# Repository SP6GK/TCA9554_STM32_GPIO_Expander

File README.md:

# TCA9554 STM32 GPIO Expander

## Software
STM32 HAL driver for the **TCA9554 8-bit I/O expander**. This is a useful IC that I find more capable and easier to use than the common PCF8574.

The project includes:
- HAL based driver
- Demo project in CubeIDE targeting the STM32F411
- KiCad project with eval PCB

### Usage
Copy the .c and .h from demo project to your project:
- TCA9554.c is in /Software/MCU/Src
- TCA9554.h is in /Software/MCU/Inc

Configure the I2C peripheral in STM32CubeMX and initialize the driver:

```c
#include "TCA9554.h"

TCA9554_HandleTypeDef GPIO_expander1 =
{
    .hi2c = &hi2c1,              // CubeMX I2C configuration
    .address = TCA9554_ADDRESS,  // Defined in header file
    .io_configuration = 0x00,    // 0 = Output, 1 = Input
    .io_states = 0x00,           // 0 = Low, 1 = High
    .pol_inversion = 0x00        // No polarity inversion
};

TCA9554_init(&GPIO_expander1);

```

By default, all pins are configured as inputs. Set `io_configuration` to configure individual pins: for example, `0b01010101` configures P0, P2, P4, and P6 as outputs, and P1, P3, P5, and P7 as inputs.

```c
uint8_t read_status = 0;
bool pin_status[8] = {0};

//Write to specific pin
for(int i = 0; i < 8; i++){
		  TCA9554_set_pin(&GPIO_expander1, i, true);
		  HAL_Delay(100);
	  }

//Write state of all pins at once
for(uint8_t counter = 0; counter < UINT8_MAX; counter++){
  TCA9554_write(&GPIO_expander1, TCA9554_OUT_REG, counter);

  read_status = TCA9554_read(&GPIO_expander1, TCA9554_IN_REG);	//Read status of every pin
  for(uint8_t i = 0; i < 8; i++){
  pin_status[i] = TCA9554_read_pin(&GPIO_expander1, i); //Read status of single pin
}

```

## Hardware

KiCad evaluation board design for the **TCA9554 I/O expander**.

The hardware project includes the schematic and PCB design files, organized under the `ECAD/` directory.
`Documents/` includes interactive BOM and .pdf schematic.

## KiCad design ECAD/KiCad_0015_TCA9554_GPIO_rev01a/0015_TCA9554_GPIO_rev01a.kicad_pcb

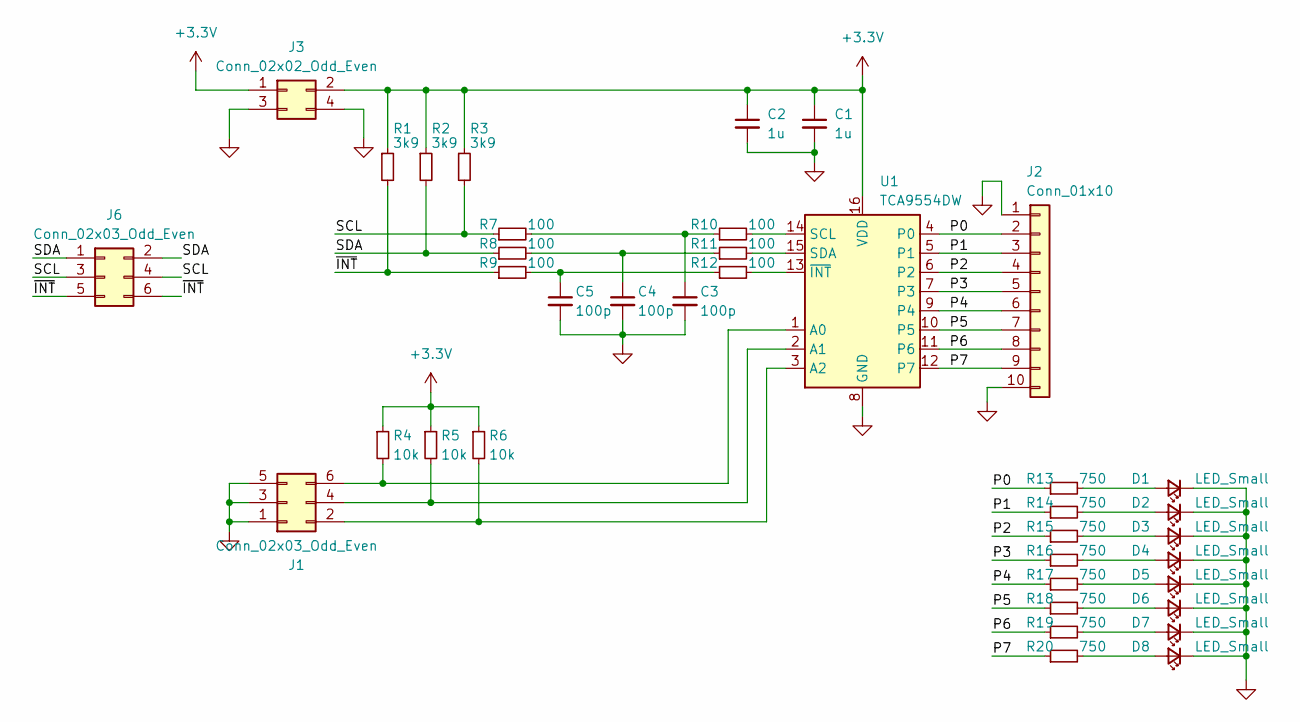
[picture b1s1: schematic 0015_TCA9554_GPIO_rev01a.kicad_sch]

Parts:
C1, C2: 1u; C_0805_2012Metric_Pad1.18x1.45mm_HandSolder
C3, C4, C5: 100p; C_0603_1608Metric_Pad1.08x0.95mm_HandSolder
D1, D2, D3, D4, D5, D6, D7, D8: LED_Small; D_0805_2012Metric_Pad1.15x1.40mm_HandSolder
J1, J6: Conn_02x03_Odd_Even; PinSocket_2x03_P2.54mm_Vertical_SMD
J2: Conn_01x10; PinHeader_1x10_P2.54mm_Vertical_SMD_Pin1Left
J3: Conn_02x02_Odd_Even; PinSocket_2x02_P2.54mm_Vertical_SMD
R1, R2, R3: 3k9; R_0603_1608Metric_Pad0.98x0.95mm_HandSolder
R4, R5, R6: 10k; R_0603_1608Metric_Pad0.98x0.95mm_HandSolder
R7, R8, R9, R10, R11, R12: 100; R_0603_1608Metric_Pad0.98x0.95mm_HandSolder
R13, R14, R15, R16, R17, R18, R19, R20: 750; R_0603_1608Metric_Pad0.98x0.95mm_HandSolder
U1: TCA9554DW; SOIC-16W_7.5x10.3mm_P1.27mm

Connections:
+3.3V: C1.1, C2.1, J3.1, J3.2, R1.1, R2.1, R3.1, R4.1, R5.1, R6.1, U1.16 (VDD)
/P0: J2.2, R13.1, U1.4 (P0)
/P1: J2.3, R14.1, U1.5 (P1)
/P2: J2.4, R15.1, U1.6 (P2)
/P3: J2.5, R16.1, U1.7 (P3)
/P4: J2.6, R17.1, U1.9 (P4)
/P5: J2.7, R18.1, U1.10 (P5)
/P6: J2.8, R19.1, U1.11 (P6)
/P7: J2.9, R20.1, U1.12 (P7)
/SCL: J6.3, J6.4, R3.2, R7.1
/SDA: J6.1, J6.2, R2.2, R8.1
/~INT: J6.5, J6.6, R1.2, R9.1
GND: C1.2, C2.2, C3.2, C4.2, C5.2, D1.1 (K), D2.1 (K), D3.1 (K), D4.1 (K), D5.1 (K), D6.1 (K), D7.1 (K), D8.1 (K), J1.1, J1.3, J1.5, J2.1, J2.10, J3.3, J3.4, U1.8 (GND)
unnamed: C3.1, R7.2, R10.1
unnamed: C4.1, R8.2, R11.1
unnamed: C5.1, R9.2, R12.1
unnamed: D1.2 (A), R13.2
unnamed: D2.2 (A), R14.2
unnamed: D3.2 (A), R15.2
unnamed: D4.2 (A), R16.2
unnamed: D5.2 (A), R17.2
unnamed: D6.2 (A), R18.2
unnamed: D7.2 (A), R19.2
unnamed: D8.2 (A), R20.2
unnamed: J1.2, R6.2, U1.3 (A2)
unnamed: J1.4, R5.2, U1.2 (A1)
unnamed: J1.6, R4.2, U1.1 (A0)
unnamed: R10.2, U1.14 (SCL)
unnamed: R11.2, U1.15 (SDA)
unnamed: R12.2, U1.13 (~INT)

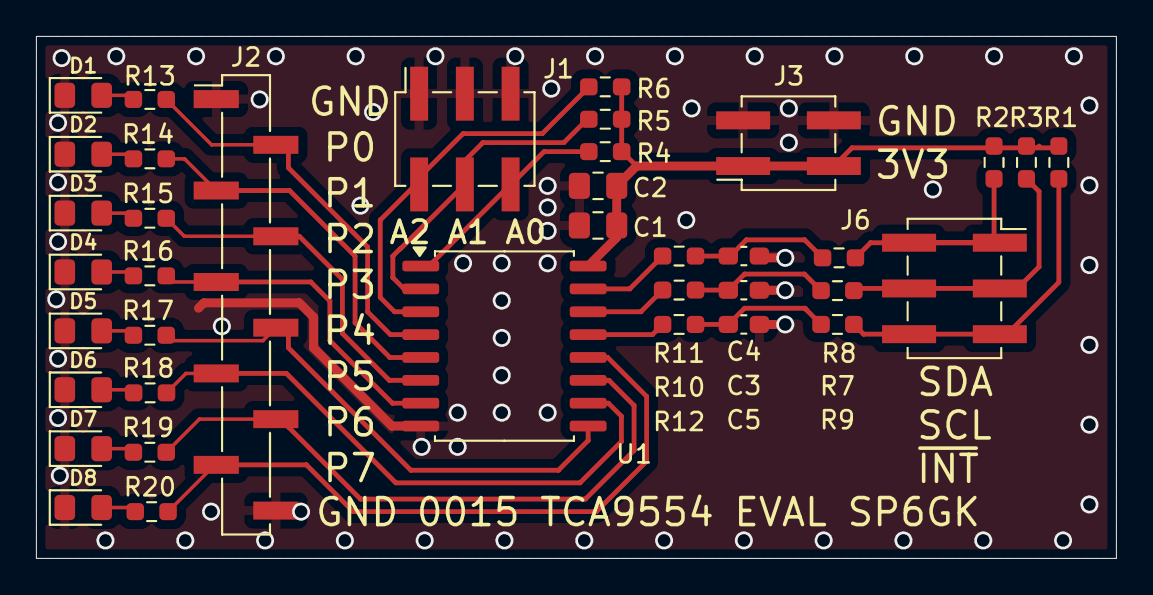
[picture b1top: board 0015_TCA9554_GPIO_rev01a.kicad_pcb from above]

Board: 2 copper layers, 60.0 x 29.0 mm, 38 parts (0 on the bottom side), 30 nets.
